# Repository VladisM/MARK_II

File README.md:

# MARK-II

MARK-II is system on chip written in VHDL, it have custom 32bit CPU and 
few custom peripherals. Also there is full featured toolchain including 
assembler, linker, emulator, c compiler and serial port loader. And, 
also there is custom FPGA board for it based on Intel MAX10 FPGA.

## Prerequisites
	
* Any common Linux distribution
* git
* texi2pdf
* pdflatex
* doxygen
* gcc
* python 2.7
* make
* quartus
* eagle

## Get more documentation

In order to get more documentation, for example reference manual for 
SoC, one can use script in root of this repository called 
`compile_doc.sh`. This will create set of some PDF files with all 
available documentation.

## Install toolchain

Toolchain can be found in folder `/toolchain`. In order to install it on 
your computer please use script in root of this repository called 
`install_toolchain.sh`.

Please check this script and optionally change value of variable `DIR`. 
In this variable should be an path to existing folder where you want to 
have toolchain installed.

At the end of installation, script will print three paths, first is 
where everything is installed and you should add this path to your PATH 
variable. Others two paths are important for compiler and linker, see 
some of one example in folder `/doc/examples` to see how to work with 
them.

## Project structure:

* **VHDL/** In this directory is all HDL sources for MARK-II SoC.
* **toolchain/** MARK-II toolchain.
* **doc/** Documentation for MARK-II.
* **board/** Board design files.

## License

Whole project, except reference manual and vbcc, is licensed under MIT 
license. Please see file LICENSE for more details. 

### Reference Manual

Reference manual is licensed under Creative Commons 
Attribution-NonCommercial 4.0 International License. 

### VBCC

Please note: vbcc is licensed by Dr. Volker Barthelmann, you can found 
full license in vbcc documentation.

My work is only backed, namely these files:

* machines/mark/machine.c
* machines/mark/machine.h
* machines/mark/machine.dt

These three files are licensed under MIT license.

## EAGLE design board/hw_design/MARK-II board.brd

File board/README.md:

MARK-II Board
=======

This directory contain design files for manufacturing official MARK-II 
Board. 

Board design is done in eagle and is located in *hw\_design*
folder. You can found schematics in pdf format located in this 
directory. 

Firmware for power management IC is in fw directory. You can found 
settings for FT230X in this directory.

Manufacturing
-----

1. **Get the PCB**

   Find service what will manufacture board for you. It have 4 layers. 
   You can use OSH Park if you wish. Board is designed against their 
   rules.

2. **Get parts and solder them**

   All parts in eagle files have attribute called mouser or farnell. 
   Export BOM and order them.
   
   Once you have all parts, go ahead and solder them. You probably want 
   to use oven or hot air, at least for FPGA, and oscillators.
   
3. **Complete it!**

   Use avr toolchain to compile and load firmware to you power 
   management IC, then use FT_Prog to load FT230X configuration. 
   Finally, compile HDL, generate pof file and configure your FPGA.
   
4. **Enjoy your board!**

   You can load examples, write your own programs, try to fight with 
   OS ... or you can make your custom case!

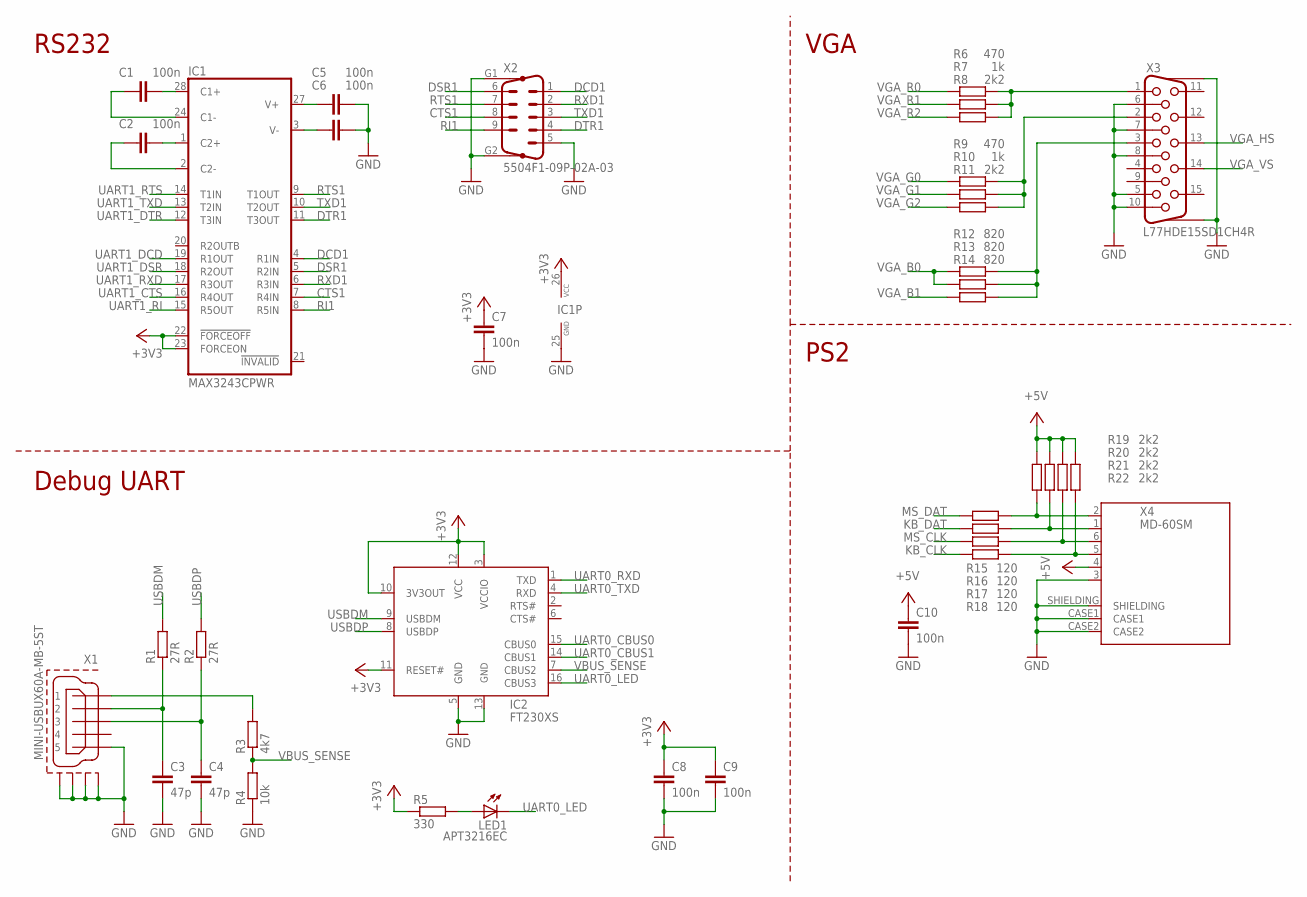
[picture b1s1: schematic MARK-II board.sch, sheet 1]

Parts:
C1, C2, C5, C6, C7, C8, C9, C10: 100n; C0603; MOUSER 710-885012206046
C3, C4: 47p; C0603; MOUSER 77-VJ0603A470JXACBC
IC1: MAX3243CPWR; TSSOP28; MOUSER 595-MAX3243CPWR
IC2: FT230XS; SSOP16; MOUSER 895-FT230XS-R
LED1: APT3216EC; 1206; MOUSER 604-APT3216EC
R1, R2: 27R; R0603; MOUSER 652-CR0603-JW-270ELF
R3: 4k7; R0603; MOUSER 603-RC0603FR-074K7L
R4: 10k; R0603; MOUSER 71-CRCW060310K0JNEAC
R5: 330; R0603; MOUSER 652-CR0603-FX3300GLF
R6, R9: 470; R0603; MOUSER 71-CRCW0603470RJNEB
R7, R10: 1k; R0603; MOUSER 71-CRCW06031K00FKEAC
R8, R11, R19, R20, R21, R22: 2k2; R0603; MOUSER 603-RC0603FR-072K2L
R12, R13, R14: 820; R0603; MOUSER 603-AC0603JR-07820RL
R15, R16, R17, R18: 120; R0603; MOUSER 652-CR0603-JW-121ELF
X1: MINI-USBUX60A-MB-5ST; UX60A-MB-5ST; MOUSER 798-UX60A-MB-5ST
X2: 5504F1-09P-02A-03; M09HP; FARNELL 1848368
X3: L77HDE15SD1CH4R; HDF15H; FARNELL 2401183
X4: MD-60SM; MINIDIN_6_3GND; MOUSER 490-MD-60SM

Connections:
+3V3: C7.1, C8.1, C9.1, IC1.22 (!FORCEOFF), IC1.23 (FORCEON), IC1.26 (VCC), IC2.3 (VCCIO), IC2.10 (3V3OUT), IC2.11 (RESET#), IC2.12 (VCC), R5.1; also elsewhere on the board
+5V: C10.1, R19.2, R20.2, R21.2, R22.2, X4.4 (5); also elsewhere on the board
CTS1: IC1.7 (R4IN), X2.8
DCD1: IC1.4 (R1IN), X2.1
DSR1: IC1.5 (R2IN), X2.6
DTR1: IC1.11 (T3OUT), X2.4
GND: C3.2, C4.2, C5.2, C6.2, C7.2, C8.2, C9.2, C10.2, IC1.25 (GND), IC2.5 (GND), IC2.13 (GND_1), R4.1, X1.5, X1.M1 (GND1), X1.M2 (GND2), X1.M3 (GND3), X1.M4 (GND4), X2.5, X2.G1, X2.G2, X3.5, X3.6, X3.7, X3.8, X3.10, X3.SCH1, X3.SCH2, X4.3 (6), X4.CASE1, X4.CASE2, X4.SHIELDING; also elsewhere on the board
KB_CLK: R18.1; also elsewhere on the board
KB_DAT: R16.1; also elsewhere on the board
MS_CLK: R17.1; also elsewhere on the board
MS_DAT: R15.1; also elsewhere on the board
unnamed: C1.2, IC1.28 (C1+)
unnamed: C2.2, IC1.1 (C2+)
unnamed: C1.1, IC1.24 (C1-)
unnamed: R16.2, R20.1, X4.1 (2)
unnamed: R12.2, R13.2, R14.2, X3.3
unnamed: C2.1, IC1.2 (C2-)
unnamed: C5.1, IC1.27 (V+)
unnamed: C6.1, IC1.3 (V-)
unnamed: R18.2, R22.1, X4.5 (4)
unnamed: R9.2, R10.2, R11.2, X3.2
unnamed: R6.2, R7.2, R8.2, X3.1
unnamed: R3.2, X1.1
unnamed: C3.1, R1.1, X1.2
unnamed: C4.1, R2.1, X1.3
unnamed: R17.2, R21.1, X4.6 (3)
unnamed: R15.2, R19.1, X4.2 (1)
unnamed: LED1.A, R5.2
RI1: IC1.8 (R5IN), X2.9
RTS1: IC1.9 (T1OUT), X2.7
RXD1: IC1.6 (R3IN), X2.2
TXD1: IC1.10 (T2OUT), X2.3
UART0_CBUS0: IC2.15 (CBUS0); also elsewhere on the board
UART0_CBUS1: IC2.14 (CBUS1); also elsewhere on the board
UART0_LED: IC2.16 (CBUS3), LED1.C; also elsewhere on the board
UART0_RXD: IC2.1 (TXD); also elsewhere on the board
UART0_TXD: IC2.4 (RXD); also elsewhere on the board
UART1_CTS: IC1.16 (R4OUT); also elsewhere on the board
UART1_DCD: IC1.19 (R1OUT); also elsewhere on the board
UART1_DSR: IC1.18 (R2OUT); also elsewhere on the board
UART1_DTR: IC1.12 (T3IN); also elsewhere on the board
UART1_RI: IC1.15 (R5OUT); also elsewhere on the board
UART1_RTS: IC1.14 (T1IN); also elsewhere on the board
UART1_RXD: IC1.17 (R3OUT); also elsewhere on the board
UART1_TXD: IC1.13 (T2IN); also elsewhere on the board
USBDM: IC2.9 (USBDM), R1.2
USBDP: IC2.8 (USBDP), R2.2
VBUS_SENSE: IC2.7 (CBUS2), R3.1, R4.2
VGA_B0: R12.1, R13.1; also elsewhere on the board
VGA_B1: R14.1; also elsewhere on the board
VGA_G0: R9.1; also elsewhere on the board
VGA_G1: R10.1; also elsewhere on the board
VGA_G2: R11.1; also elsewhere on the board
VGA_HS: X3.13; also elsewhere on the board
VGA_R0: R6.1; also elsewhere on the board
VGA_R1: R7.1; also elsewhere on the board
VGA_R2: R8.1; also elsewhere on the board
VGA_VS: X3.14; also elsewhere on the board

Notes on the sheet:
RS232
Debug UART
VGA
PS2

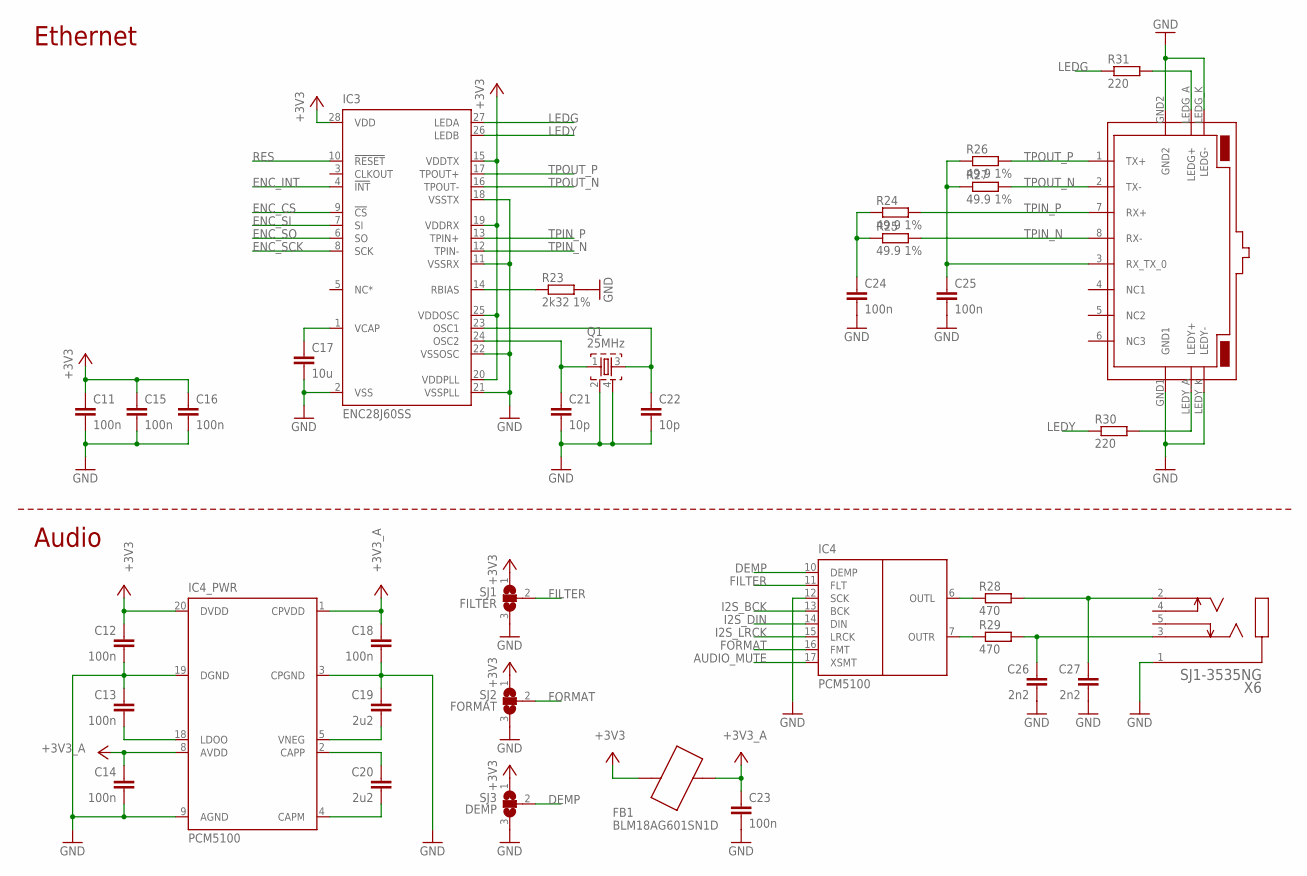
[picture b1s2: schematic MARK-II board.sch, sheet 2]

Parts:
C11, C12, C13, C14, C15, C16, C18, C23, C24, C25: 100n; C0603; MOUSER 710-885012206046
C17: 10u; C0603; MOUSER 963-LMK107BBJ106KALT
C19, C20: 2u2; C0603; MOUSER 81-GRM188R61E225KA2D
C21, C22: 10p; C0603; MOUSER 710-885012006017
C26, C27: 2n2; C0603; MOUSER 710-885012206085
FB1: BLM18AG601SN1D; R0603; MOUSER 81-BLM11A601S
IC3: ENC28J60SS; SSOP28; MOUSER 579-ENC28J60-I/SS
IC4: PCM5100; TSSOP20; MOUSER 595-PCM5100APWR
Q1: 25MHz; 3.4X2.7-4-PAD; MOUSER 449-LFXTAL035268REEL
R23: 2k32 1%; R0603; MOUSER 603-RC0603FR-072K32L
R24, R25, R26, R27: 49.9 1%; R0603; MOUSER 603-RC0603FR-0749R9L
R28, R29: 470; R0603; MOUSER 71-CRCW0603470RJNEB
R30, R31: 220; R0603; MOUSER 71-CRCW0603220RFKEB
SJ1: FILTER; SJ_2
SJ2: FORMAT; SJ_2
SJ3: DEMP; SJ_2
X5: RB1-125BAG1A; MOUSER 950-RB1-125BAG1A
X6: SJ1-3535NG; JACK; MOUSER 490-SJ1-3535NG-GR

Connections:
+3V3: C11.1, C12.1, C15.1, C16.1, FB1.1, IC3.15 (VDDTX), IC3.19 (VDDRX), IC3.20 (VDDPLL), IC3.25 (VDDOSC), IC3.28 (VDD), IC4.20 (DVDD), SJ1.1, SJ2.1, SJ3.1; also elsewhere on the board
+3V3_A: C14.1, C18.1, C23.1, FB1.2, IC4.1 (CPVDD), IC4.8 (AVDD)
AUDIO_MUTE: IC4.17 (XSMT); also elsewhere on the board
DEMP: IC4.10 (DEMP), SJ3.2
ENC_CS: IC3.9 (!CS); also elsewhere on the board
ENC_INT: IC3.4 (!INT); also elsewhere on the board
ENC_SCK: IC3.8 (SCK); also elsewhere on the board
ENC_SI: IC3.7 (SI); also elsewhere on the board
ENC_SO: IC3.6 (SO); also elsewhere on the board
FILTER: IC4.11 (FLT), SJ1.2
FORMAT: IC4.16 (FMT), SJ2.2
GND: C11.2, C12.2, C13.1, C14.2, C15.2, C16.2, C17.2, C18.2, C19.1, C21.2, C22.2, C23.2, C24.2, C25.2, C26.2, C27.2, IC3.2 (VSS), IC3.11 (VSSRX), IC3.18 (VSSTX), IC3.21 (VSSPLL), IC3.22 (VSSOSC), IC4.3 (CPGND), IC4.9 (AGND), IC4.12 (SCK), IC4.19 (DGND), Q1.2, Q1.4, R23.2, SJ1.3, SJ2.3, SJ3.3, X5.GND1, X5.GND2, X5.LEDG_K (LEDG-), X5.LEDY_K (LEDY-), X6.1 (SLEEVE); also elsewhere on the board
I2S_BCK: IC4.13 (BCK); also elsewhere on the board
I2S_DIN: IC4.14 (DIN); also elsewhere on the board
I2S_LRCK: IC4.15 (LRCK); also elsewhere on the board
LEDG: IC3.27 (LEDA), R31.1
LEDY: IC3.26 (LEDB), R30.1
unnamed: C24.1, R24.1, R25.1
unnamed: C17.1, IC3.1 (VCAP)
unnamed: R30.2, X5.LEDY_A (LEDY+)
unnamed: R31.2, X5.LEDG_A (LEDG+)
unnamed: C25.1, R26.1, R27.1, X5.3 (RX_TX_0)
unnamed: IC3.14 (RBIAS), R23.1
unnamed: C21.1, IC3.24 (OSC2), Q1.1
unnamed: C22.1, IC3.23 (OSC1), Q1.3
unnamed: C20.1, IC4.2 (CAPP)
unnamed: C20.2, IC4.4 (CAPM)
unnamed: C13.2, IC4.18 (LDOO)
unnamed: IC4.6 (OUTL), R28.1
unnamed: IC4.7 (OUTR), R29.1
unnamed: C27.1, R28.2, X6.2 (TIP)
unnamed: C26.1, R29.2, X6.3 (RING)
unnamed: C19.2, IC4.5 (VNEG)
RES: IC3.10 (!RESET); also elsewhere on the board
TPIN_N: IC3.12 (TPIN-), R25.2, X5.8 (RX-)
TPIN_P: IC3.13 (TPIN+), R24.2, X5.7 (RX+)
TPOUT_N: IC3.16 (TPOUT-), R27.2, X5.2 (TX-)
TPOUT_P: IC3.17 (TPOUT+), R26.2, X5.1 (TX+)

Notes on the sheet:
Ethernet
Audio

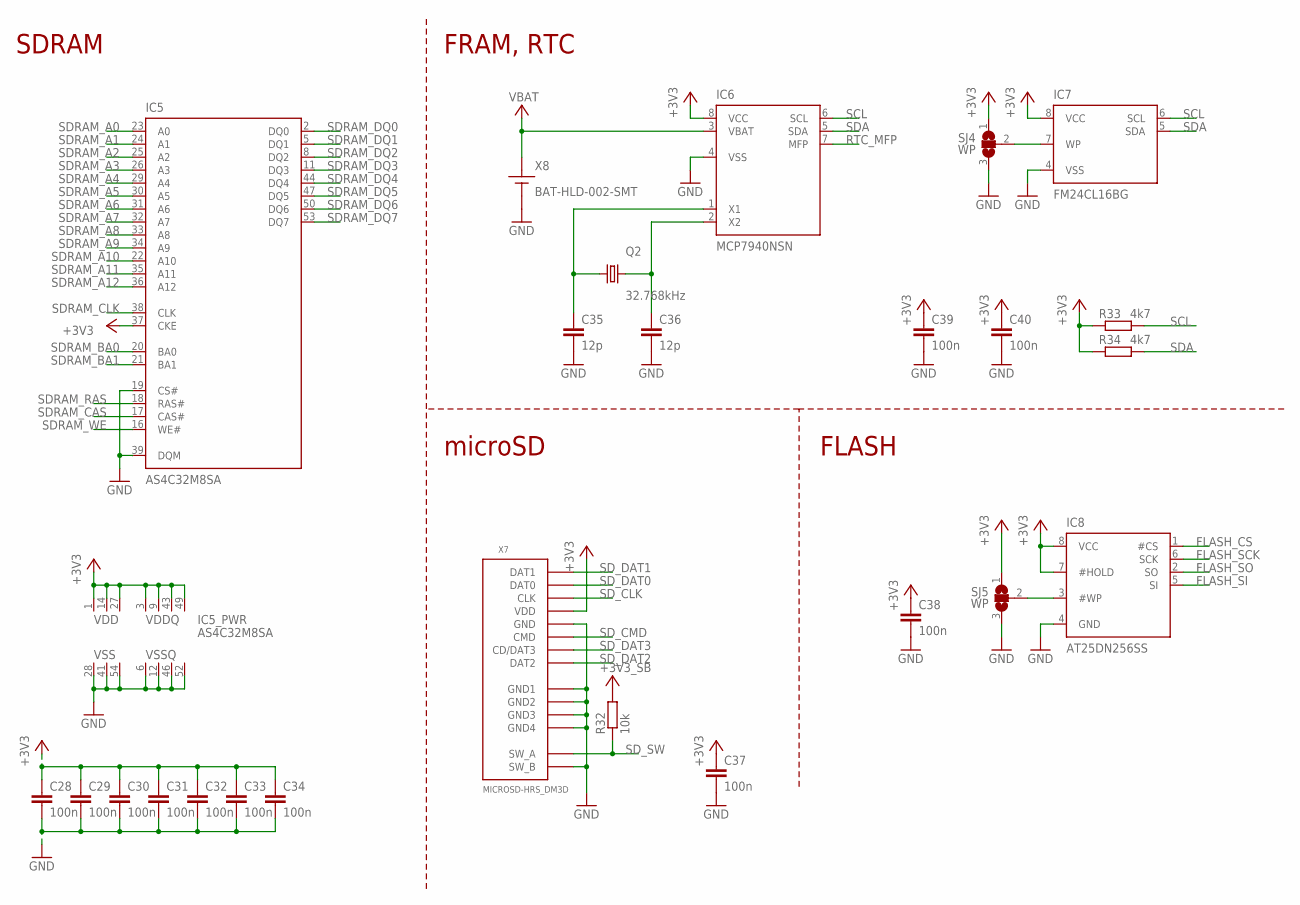
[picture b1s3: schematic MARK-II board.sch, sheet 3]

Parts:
C28, C29, C30, C31, C32, C33, C34, C37, C38, C39, C40: 100n; C0603; MOUSER 710-885012206046
C35, C36: 12p; C0603; MOUSER 77-VJ0603A120JXACBC
IC5: AS4C32M8SA; TSOP54; MOUSER 913-AS4C32M8SA6TIN
IC6: MCP7940NSN; SOIC8; MOUSER 579-MCP7940N-I/SN
IC7: FM24CL16BG; SOIC8; MOUSER 877-FM24CL16B-G
IC8: AT25DN256SS; SOIC8; MOUSER 988-AT25DN256-SSHF-B
Q2: 32.768kHz; 85SMX; MOUSER 449-LFXTAL003000REEL
R32: 10k; R0603; MOUSER 71-CRCW060310K0JNEAC
R33, R34: 4k7; R0603; MOUSER 603-RC0603FR-074K7L
SJ4, SJ5: WP; SJ_2
X7: MICROSD-HRS_DM3D; DM3D; MOUSER 798-DM3D-SF
X8: BAT-HLD-002-SMT; MOUSER 712-BAT-HLD-002-SMT

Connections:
+3V3: C28.1, C29.1, C30.1, C31.1, C32.1, C33.1, C34.1, C37.1, C38.1, C39.1, C40.1, IC5.1 (VDD0), IC5.3 (VDDQ0), IC5.9 (VDDQ1), IC5.14 (VDD1), IC5.27 (VDD2), IC5.37 (CKE), IC5.43 (VDDQ2), IC5.49 (VDDQ3), IC6.8 (VCC), IC7.8 (VCC), IC8.7 (#HOLD), IC8.8 (VCC), R33.1, R34.1, SJ4.1, SJ5.1, X7.VDD; also elsewhere on the board
+3V3_SB: R32.2; also elsewhere on the board
FLASH_CS: IC8.1 (#CS); also elsewhere on the board
FLASH_SCK: IC8.6 (SCK); also elsewhere on the board
FLASH_SI: IC8.5 (SI); also elsewhere on the board
FLASH_SO: IC8.2 (SO); also elsewhere on the board
GND: C28.2, C29.2, C30.2, C31.2, C32.2, C33.2, C34.2, C35.2, C36.2, C37.2, C38.2, C39.2, C40.2, IC5.6 (VSSQ0), IC5.12 (VSSQ1), IC5.19 (CS#), IC5.28 (VSS0), IC5.39 (DQM), IC5.41 (VSS1), IC5.46 (VSSQ2), IC5.52 (VSSQ3), IC5.54 (VSS2), IC6.4 (VSS), IC7.4 (VSS), IC8.4 (GND), SJ4.3, SJ5.3, X7.GND1, X7.GND2, X7.GND3, X7.GND4, X7.SW_B, X7.VSS (GND), X8.N; also elsewhere on the board
unnamed: C35.1, IC6.1 (X1), Q2.4 (2)
unnamed: C36.1, IC6.2 (X2), Q2.1
unnamed: IC7.7 (WP), SJ4.2
unnamed: IC8.3 (#WP), SJ5.2
RTC_MFP: IC6.7 (MFP); also elsewhere on the board
SCL: IC6.6 (SCL), IC7.6 (SCL), R33.2; also elsewhere on the board
SDA: IC6.5 (SDA), IC7.5 (SDA), R34.2; also elsewhere on the board
SDRAM_A0: IC5.23 (A0); also elsewhere on the board
SDRAM_A1: IC5.24 (A1); also elsewhere on the board
SDRAM_A2: IC5.25 (A2); also elsewhere on the board
SDRAM_A3: IC5.26 (A3); also elsewhere on the board
SDRAM_A4: IC5.29 (A4); also elsewhere on the board
SDRAM_A5: IC5.30 (A5); also elsewhere on the board
SDRAM_A6: IC5.31 (A6); also elsewhere on the board
SDRAM_A7: IC5.32 (A7); also elsewhere on the board
SDRAM_A8: IC5.33 (A8); also elsewhere on the board
SDRAM_A9: IC5.34 (A9); also elsewhere on the board
SDRAM_A10: IC5.22 (A10); also elsewhere on the board
SDRAM_A11: IC5.35 (A11); also elsewhere on the board
SDRAM_A12: IC5.36 (A12); also elsewhere on the board
SDRAM_BA0: IC5.20 (BA0); also elsewhere on the board
SDRAM_BA1: IC5.21 (BA1); also elsewhere on the board
SDRAM_CAS: IC5.17 (CAS#); also elsewhere on the board
SDRAM_CLK: IC5.38 (CLK); also elsewhere on the board
SDRAM_DQ0: IC5.2 (DQ0); also elsewhere on the board
SDRAM_DQ1: IC5.5 (DQ1); also elsewhere on the board
SDRAM_DQ2: IC5.8 (DQ2); also elsewhere on the board
SDRAM_DQ3: IC5.11 (DQ3); also elsewhere on the board
SDRAM_DQ4: IC5.44 (DQ4); also elsewhere on the board
SDRAM_DQ5: IC5.47 (DQ5); also elsewhere on the board
SDRAM_DQ6: IC5.50 (DQ6); also elsewhere on the board
SDRAM_DQ7: IC5.53 (DQ7); also elsewhere on the board
SDRAM_RAS: IC5.18 (RAS#); also elsewhere on the board
SDRAM_WE: IC5.16 (WE#); also elsewhere on the board
SD_CLK: X7.CLK; also elsewhere on the board
SD_CMD: X7.CMD; also elsewhere on the board
SD_DAT0: X7.DAT0; also elsewhere on the board
SD_DAT1: X7.DAT1; also elsewhere on the board
SD_DAT2: X7.DAT2; also elsewhere on the board
SD_DAT3: X7.CD/DAT3; also elsewhere on the board
SD_SW: R32.1, X7.SW_A; also elsewhere on the board
VBAT: IC6.3 (VBAT), X8.P1; also elsewhere on the board

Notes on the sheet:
SDRAM
microSD
FLASH
FRAM, RTC

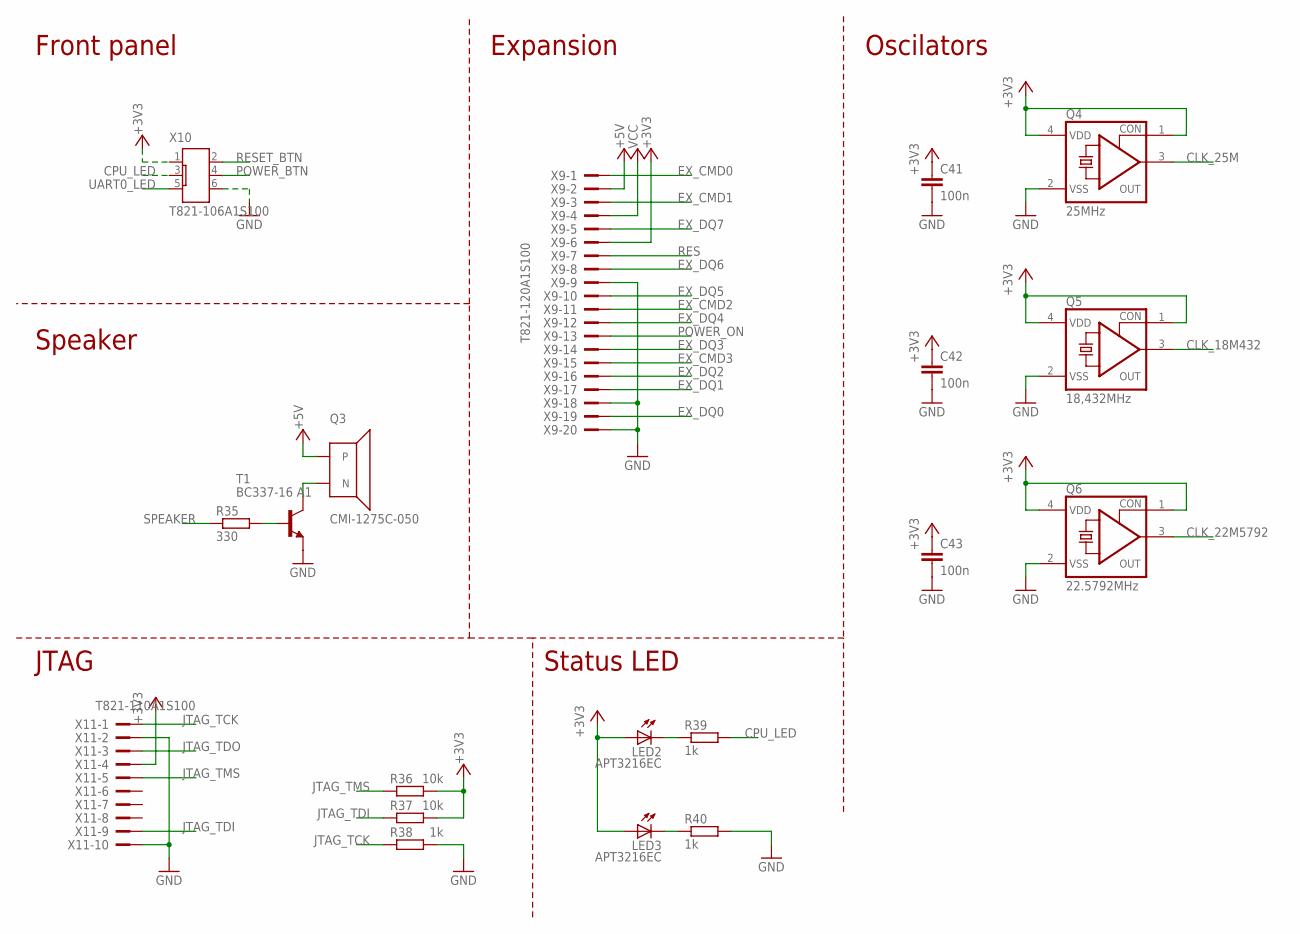
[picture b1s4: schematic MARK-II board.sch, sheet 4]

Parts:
C41, C42, C43: 100n; C0603; MOUSER 710-885012206046
LED2, LED3: APT3216EC; 1206; MOUSER 604-APT3216EC
Q3: CMI-1275C-050; BUUZZER; MOUSER 490-CMI-1275C-050
Q4: 25MHz; 5.2X3.4-4-PAD; MOUSER 449-LFSPXO018077REEL
Q5: 18,432MHz; 5.2X3.4-4-PAD; MOUSER 449-LFSPXO021101REEL
Q6: 22.5792MHz; 5.2X3.4-4-PAD; MOUSER 449-LFSPXO023492BULK
R35: 330; R0603; MOUSER 652-CR0603-FX3300GLF
R36, R37: 10k; R0603; MOUSER 71-CRCW060310K0JNEAC
R38, R39, R40: 1k; R0603; MOUSER 71-CRCW06031K00FKEAC
T1: BC337-16 A1; TO92; MOUSER 821-BC337-16-A1
X9: T821-120A1S100; PAK100/2500-20; FARNELL 2215309
X10: T821-106A1S100; PAK100/2300-06; FARNELL 2215302
X11: T821-110A1S100; PAK100/2500-10; FARNELL 2215304

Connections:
+3V3: C41.1, C42.1, C43.1, LED2.A, LED3.A, Q4.1 (CON), Q4.4 (VDD), Q5.1 (CON), Q5.4 (VDD), Q6.1 (CON), Q6.4 (VDD), R36.2, R37.2, X9.6, X10.1, X11.4; also elsewhere on the board
+5V: Q3.P, X9.2; also elsewhere on the board
CLK_18M432: Q5.3 (OUT); also elsewhere on the board
CLK_22M5792: Q6.3 (OUT); also elsewhere on the board
CLK_25M: Q4.3 (OUT); also elsewhere on the board
CPU_LED: R39.2, X10.3; also elsewhere on the board
EX_CMD0: X9.1; also elsewhere on the board
EX_CMD1: X9.3; also elsewhere on the board
EX_CMD2: X9.11; also elsewhere on the board
EX_CMD3: X9.15; also elsewhere on the board
EX_DQ0: X9.19; also elsewhere on the board
EX_DQ1: X9.17; also elsewhere on the board
EX_DQ2: X9.16; also elsewhere on the board
EX_DQ3: X9.14; also elsewhere on the board
EX_DQ4: X9.12; also elsewhere on the board
EX_DQ5: X9.10; also elsewhere on the board
EX_DQ6: X9.8; also elsewhere on the board
EX_DQ7: X9.5; also elsewhere on the board
GND: C41.2, C42.2, C43.2, Q4.2 (VSS), Q5.2 (VSS), Q6.2 (VSS), R38.2, R40.2, T1.1 (E), X9.9, X9.18, X9.20, X10.6, X11.2, X11.10; also elsewhere on the board
JTAG_TCK: R38.1, X11.1; also elsewhere on the board
JTAG_TDI: R37.1, X11.9; also elsewhere on the board
JTAG_TDO: X11.3; also elsewhere on the board
JTAG_TMS: R36.1, X11.5; also elsewhere on the board
unnamed: LED3.C, R40.1
unnamed: LED2.C, R39.1
unnamed: Q3.N, T1.3 (C)
unnamed: R35.2, T1.2 (B)
POWER_BTN: X10.4; also elsewhere on the board
POWER_ON: X9.13; also elsewhere on the board
RES: X9.7; also elsewhere on the board
RESET_BTN: X10.2; also elsewhere on the board
SPEAKER: R35.1; also elsewhere on the board
UART0_LED: X10.5; also elsewhere on the board
VCC: X9.4; also elsewhere on the board

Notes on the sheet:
JTAG
Status LED
Oscilators
Speaker
Expansion
Front panel

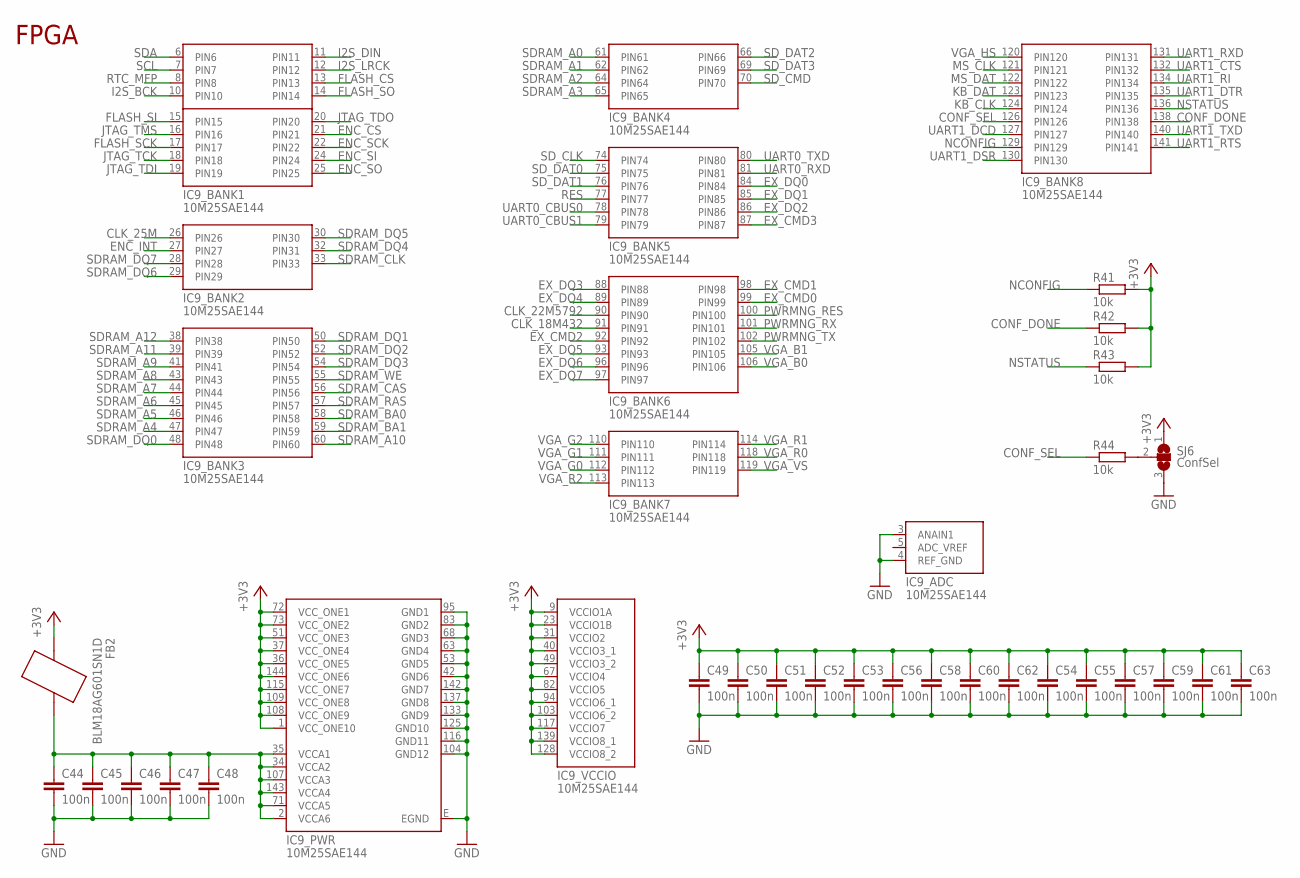
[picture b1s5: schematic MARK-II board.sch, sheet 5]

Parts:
C44, C45, C46, C47, C48, C49, C50, C51, C52, C53, C54, C55, C56, C57, C58, C59, C60, C61, C62, C63: 100n; C0603; MOUSER 710-885012206046
FB2: BLM18AG601SN1D; R0603; MOUSER 81-BLM11A601S
IC9: 10M25SAE144; EQFP144; MOUSER 989-10M25SAE144C8G
R41, R42, R43, R44: 10k; R0603; MOUSER 71-CRCW060310K0JNEAC
SJ6: ConfSel; SJ_2

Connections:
+3V3: C49.1, C50.1, C51.1, C52.1, C53.1, C54.1, C55.1, C56.1, C57.1, C58.1, C59.1, C60.1, C61.1, C62.1, C63.1, FB2.1, IC9.1 (VCC_ONE10), IC9.9 (VCCIO1A), IC9.23 (VCCIO1B), IC9.31 (VCCIO2), IC9.36 (VCC_ONE5), IC9.37 (VCC_ONE4), IC9.40 (VCCIO3_1), IC9.49 (VCCIO3_2), IC9.51 (VCC_ONE3), IC9.67 (VCCIO4), IC9.72 (VCC_ONE1), IC9.73 (VCC_ONE2), IC9.82 (VCCIO5), IC9.94 (VCCIO6_1), IC9.103 (VCCIO6_2), IC9.108 (VCC_ONE9), IC9.109 (VCC_ONE8), IC9.115 (VCC_ONE7), IC9.117 (VCCIO7), IC9.128 (VCCIO8_2), IC9.139 (VCCIO8_1), IC9.144 (VCC_ONE6), R41.2, R42.2, R43.2, SJ6.1; also elsewhere on the board
CLK_18M432: IC9.91 (PIN91); also elsewhere on the board
CLK_22M5792: IC9.90 (PIN90); also elsewhere on the board
CLK_25M: IC9.26 (PIN26); also elsewhere on the board
CONF_DONE: IC9.138 (PIN138), R42.1
CONF_SEL: IC9.126 (PIN126), R44.1
ENC_CS: IC9.21 (PIN21); also elsewhere on the board
ENC_INT: IC9.27 (PIN27); also elsewhere on the board
ENC_SCK: IC9.22 (PIN22); also elsewhere on the board
ENC_SI: IC9.24 (PIN24); also elsewhere on the board
ENC_SO: IC9.25 (PIN25); also elsewhere on the board
EX_CMD0: IC9.99 (PIN99); also elsewhere on the board
EX_CMD1: IC9.98 (PIN98); also elsewhere on the board
EX_CMD2: IC9.92 (PIN92); also elsewhere on the board
EX_CMD3: IC9.87 (PIN87); also elsewhere on the board
EX_DQ0: IC9.84 (PIN84); also elsewhere on the board
EX_DQ1: IC9.85 (PIN85); also elsewhere on the board
EX_DQ2: IC9.86 (PIN86); also elsewhere on the board
EX_DQ3: IC9.88 (PIN88); also elsewhere on the board
EX_DQ4: IC9.89 (PIN89); also elsewhere on the board
EX_DQ5: IC9.93 (PIN93); also elsewhere on the board
EX_DQ6: IC9.96 (PIN96); also elsewhere on the board
EX_DQ7: IC9.97 (PIN97); also elsewhere on the board
FLASH_CS: IC9.13 (PIN13); also elsewhere on the board
FLASH_SCK: IC9.17 (PIN17); also elsewhere on the board
FLASH_SI: IC9.15 (PIN15); also elsewhere on the board
FLASH_SO: IC9.14 (PIN14); also elsewhere on the board
GND: C44.2, C45.2, C46.2, C47.2, C48.2, C49.2, C50.2, C51.2, C52.2, C53.2, C54.2, C55.2, C56.2, C57.2, C58.2, C59.2, C60.2, C61.2, C62.2, C63.2, IC9.3 (ANAIN1), IC9.4 (REF_GND), IC9.42 (GND6), IC9.53 (GND5), IC9.63 (GND4), IC9.68 (GND3), IC9.83 (GND2), IC9.95 (GND1), IC9.104 (GND12), IC9.116 (GND11), IC9.125 (GND10), IC9.133 (GND9), IC9.137 (GND8), IC9.142 (GND7), IC9.E (EGND), SJ6.3; also elsewhere on the board
I2S_BCK: IC9.10 (PIN10); also elsewhere on the board
I2S_DIN: IC9.11 (PIN11); also elsewhere on the board
I2S_LRCK: IC9.12 (PIN12); also elsewhere on the board
JTAG_TCK: IC9.18 (PIN18); also elsewhere on the board
JTAG_TDI: IC9.19 (PIN19); also elsewhere on the board
JTAG_TDO: IC9.20 (PIN20); also elsewhere on the board
JTAG_TMS: IC9.16 (PIN16); also elsewhere on the board
KB_CLK: IC9.124 (PIN124); also elsewhere on the board
KB_DAT: IC9.123 (PIN123); also elsewhere on the board
MS_CLK: IC9.121 (PIN121); also elsewhere on the board
MS_DAT: IC9.122 (PIN122); also elsewhere on the board
unnamed: R44.2, SJ6.2
NCONFIG: IC9.129 (PIN129), R41.1
NSTATUS: IC9.136 (PIN136), R43.1
PWRMNG_RES: IC9.100 (PIN100); also elsewhere on the board
PWRMNG_RX: IC9.101 (PIN101); also elsewhere on the board
PWRMNG_TX: IC9.102 (PIN102); also elsewhere on the board
RES: IC9.77 (PIN77); also elsewhere on the board
RTC_MFP: IC9.8 (PIN8); also elsewhere on the board
SCL: IC9.7 (PIN7); also elsewhere on the board
SDA: IC9.6 (PIN6); also elsewhere on the board
SDRAM_A0: IC9.61 (PIN61); also elsewhere on the board
SDRAM_A1: IC9.62 (PIN62); also elsewhere on the board
SDRAM_A2: IC9.64 (PIN64); also elsewhere on the board
SDRAM_A3: IC9.65 (PIN65); also elsewhere on the board
SDRAM_A4: IC9.47 (PIN47); also elsewhere on the board
SDRAM_A5: IC9.46 (PIN46); also elsewhere on the board
SDRAM_A6: IC9.45 (PIN45); also elsewhere on the board
SDRAM_A7: IC9.44 (PIN44); also elsewhere on the board
SDRAM_A8: IC9.43 (PIN43); also elsewhere on the board
SDRAM_A9: IC9.41 (PIN41); also elsewhere on the board
SDRAM_A10: IC9.60 (PIN60); also elsewhere on the board
SDRAM_A11: IC9.39 (PIN39); also elsewhere on the board
SDRAM_A12: IC9.38 (PIN38); also elsewhere on the board
SDRAM_BA0: IC9.58 (PIN58); also elsewhere on the board
SDRAM_BA1: IC9.59 (PIN59); also elsewhere on the board
SDRAM_CAS: IC9.56 (PIN56); also elsewhere on the board
SDRAM_CLK: IC9.33 (PIN33); also elsewhere on the board
SDRAM_DQ0: IC9.48 (PIN48); also elsewhere on the board
SDRAM_DQ1: IC9.50 (PIN50); also elsewhere on the board
SDRAM_DQ2: IC9.52 (PIN52); also elsewhere on the board
SDRAM_DQ3: IC9.54 (PIN54); also elsewhere on the board
SDRAM_DQ4: IC9.32 (PIN31); also elsewhere on the board
SDRAM_DQ5: IC9.30 (PIN30); also elsewhere on the board
SDRAM_DQ6: IC9.29 (PIN29); also elsewhere on the board
SDRAM_DQ7: IC9.28 (PIN28); also elsewhere on the board
SDRAM_RAS: IC9.57 (PIN57); also elsewhere on the board
SDRAM_WE: IC9.55 (PIN55); also elsewhere on the board
SD_CLK: IC9.74 (PIN74); also elsewhere on the board
SD_CMD: IC9.70 (PIN70); also elsewhere on the board
SD_DAT0: IC9.75 (PIN75); also elsewhere on the board
SD_DAT1: IC9.76 (PIN76); also elsewhere on the board
SD_DAT2: IC9.66 (PIN66); also elsewhere on the board
SD_DAT3: IC9.69 (PIN69); also elsewhere on the board
UART0_CBUS0: IC9.78 (PIN78); also elsewhere on the board
UART0_CBUS1: IC9.79 (PIN79); also elsewhere on the board
UART0_RXD: IC9.81 (PIN81); also elsewhere on the board
UART0_TXD: IC9.80 (PIN80); also elsewhere on the board
UART1_CTS: IC9.132 (PIN132); also elsewhere on the board
UART1_DCD: IC9.127 (PIN127); also elsewhere on the board
UART1_DSR: IC9.130 (PIN130); also elsewhere on the board
UART1_DTR: IC9.135 (PIN135); also elsewhere on the board
UART1_RI: IC9.134 (PIN134); also elsewhere on the board
UART1_RTS: IC9.141 (PIN141); also elsewhere on the board
UART1_RXD: IC9.131 (PIN131); also elsewhere on the board
UART1_TXD: IC9.140 (PIN140); also elsewhere on the board
VCCA: C44.1, C45.1, C46.1, C47.1, C48.1, FB2.2, IC9.2 (VCCA6), IC9.34 (VCCA2), IC9.35 (VCCA1), IC9.71 (VCCA5), IC9.107 (VCCA3), IC9.143 (VCCA4)
VGA_B0: IC9.106 (PIN106); also elsewhere on the board
VGA_B1: IC9.105 (PIN105); also elsewhere on the board
VGA_G0: IC9.112 (PIN112); also elsewhere on the board
VGA_G1: IC9.111 (PIN111); also elsewhere on the board
VGA_G2: IC9.110 (PIN110); also elsewhere on the board
VGA_HS: IC9.120 (PIN120); also elsewhere on the board
VGA_R0: IC9.118 (PIN118); also elsewhere on the board
VGA_R1: IC9.114 (PIN114); also elsewhere on the board
VGA_R2: IC9.113 (PIN113); also elsewhere on the board
VGA_VS: IC9.119 (PIN119); also elsewhere on the board

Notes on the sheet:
FPGA

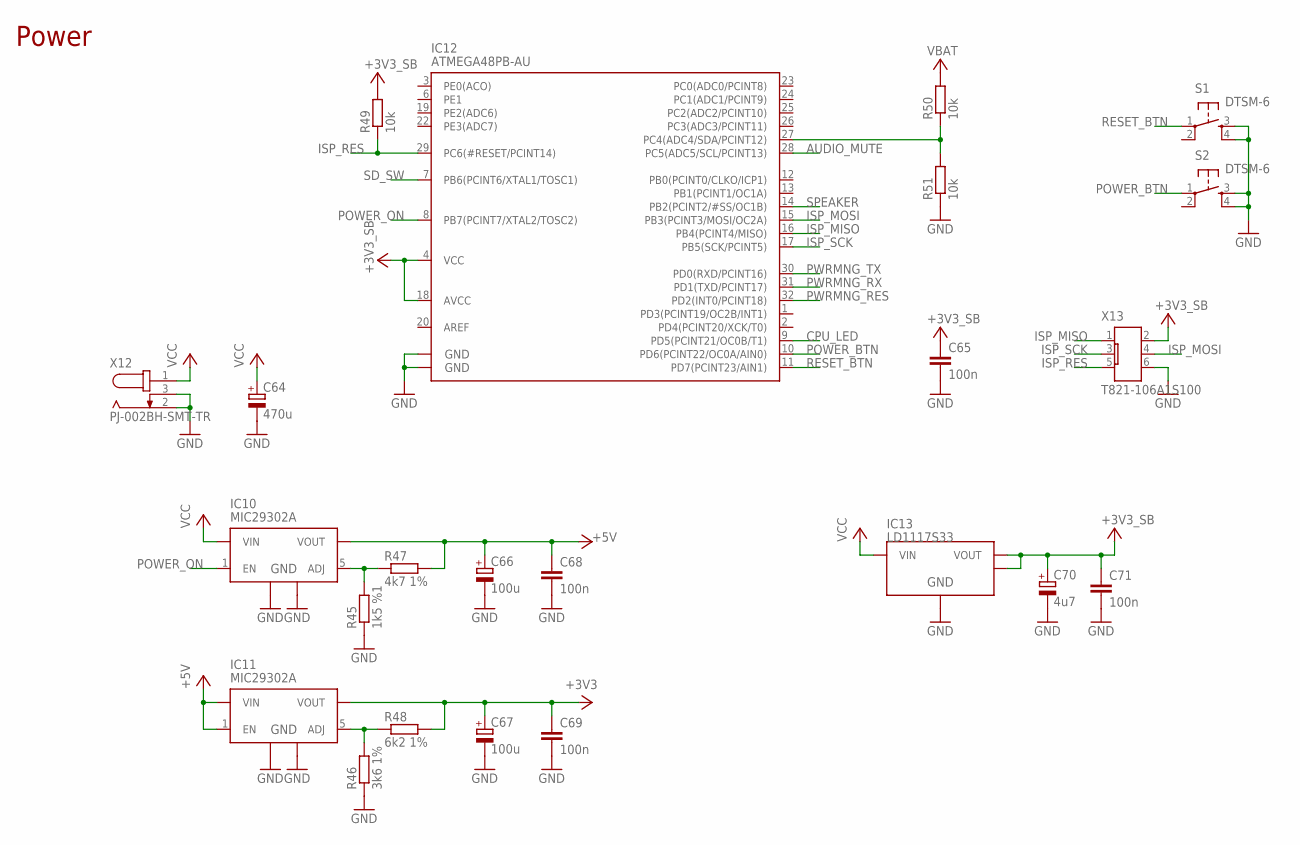
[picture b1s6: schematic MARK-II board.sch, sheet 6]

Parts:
C64: 470u; E3,5-8; MOUSER 667-EEU-FR1E471Y
C65, C68, C69, C71: 100n; C0603; MOUSER 710-885012206046
C66, C67: 100u; E2,5-7; MOUSER 140-RGA101M1EBK0611G
C70: 4u7; E2,5-5; MOUSER 667-ECA-1HM4R7I
IC10, IC11: MIC29302A; D2PAK-5; MOUSER 998-MIC29302AWU
IC12: ATMEGA48PB-AU; TQFP32-08; MOUSER 556-ATMEGA48PB-AU
IC13: LD1117S33; SOT223; MOUSER 511-LD1117S33
R45: 1k5 %1; R0603; MOUSER 71-CRCW06031K50FKEB
R46: 3k6 1%; R0603; MOUSER 603-RC0603FR-073K6L
R47: 4k7 1%; R0603; MOUSER 603-RC0603FR-074K7L
R48: 6k2 1%; R0603; MOUSER 652-CR0603FX-6201ELF
R49, R50, R51: 10k; R0603; MOUSER 71-CRCW060310K0JNEAC
S1, S2: DTSM-6; FARNELL 2396053
X12: PJ-002BH-SMT-TR; PJ-002BH-SMT; MOUSER 490-PJ-002BH-SMT-TR
X13: T821-106A1S100; PAK100/2300-06; FARNELL 2215302

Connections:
+3V3: C67.+, C69.1, IC11.4 (VOUT), R48.2; also elsewhere on the board
+3V3_SB: C65.1, C70.+, C71.1, IC12.4 (VCC), IC12.18 (AVCC), IC13.2 (VOUT), IC13.4, R49.2, X13.2; also elsewhere on the board
+5V: C66.+, C68.1, IC10.4 (VOUT), IC11.1 (EN), IC11.2 (VIN), R47.2; also elsewhere on the board
AUDIO_MUTE: IC12.28 (PC5(ADC5/SCL/PCINT13)); also elsewhere on the board
CPU_LED: IC12.9 (PD5(PCINT21/OC0B/T1)); also elsewhere on the board
GND: C64.-, C65.2, C66.-, C67.-, C68.2, C69.2, C70.-, C71.2, IC10.3 (GND), IC10.P, IC11.3 (GND), IC11.P, IC12.5 (GND), IC12.21 (GND), IC13.1 (GND), R45.1, R46.1, R51.1, S1.3, S1.4, S2.3, S2.4, X12.2 (1), X12.3 (2), X13.6; also elsewhere on the board
ISP_MISO: IC12.16 (PB4(PCINT4/MISO)), X13.1
ISP_MOSI: IC12.15 (PB3(PCINT3/MOSI/OC2A)), X13.4
ISP_RES: IC12.29 (PC6(#RESET/PCINT14)), R49.1, X13.5
ISP_SCK: IC12.17 (PB5(SCK/PCINT5)), X13.3
unnamed: IC12.27 (PC4(ADC4/SDA/PCINT12)), R50.1, R51.2
unnamed: IC11.5 (ADJ), R46.2, R48.1
unnamed: IC10.5 (ADJ), R45.2, R47.1
POWER_BTN: IC12.10 (PD6(PCINT22/OC0A/AIN0)), S2.1; also elsewhere on the board
POWER_ON: IC10.1 (EN), IC12.8 (PB7(PCINT7/XTAL2/TOSC2)); also elsewhere on the board
PWRMNG_RES: IC12.32 (PD2(INT0/PCINT18)); also elsewhere on the board
PWRMNG_RX: IC12.31 (PD1(TXD/PCINT17)); also elsewhere on the board
PWRMNG_TX: IC12.30 (PD0(RXD/PCINT16)); also elsewhere on the board
RESET_BTN: IC12.11 (PD7(PCINT23/AIN1)), S1.1; also elsewhere on the board
SD_SW: IC12.7 (PB6(PCINT6/XTAL1/TOSC1)); also elsewhere on the board
SPEAKER: IC12.14 (PB2(PCINT2/#SS/OC1B)); also elsewhere on the board
VBAT: R50.2; also elsewhere on the board
VCC: C64.+, IC10.2 (VIN), IC13.3 (VIN), X12.1 (3); also elsewhere on the board

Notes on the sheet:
Power
